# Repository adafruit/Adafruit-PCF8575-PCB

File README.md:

## Adafruit PCF8575 I2C 16 GPIO Expander PCB

<a href="http://www.adafruit.com/products/5611"><br/>
Click here to purchase one from the Adafruit shop</a>

PCB files for the Adafruit PCF8575 I2C 16 GPIO Expander. 

Format is EagleCAD schematic and board layout
* https://www.adafruit.com/product/5611

### Description

Expand your project possibilities, with the Adafruit PCF8575 GPIO Expander Breakout - an affordable 16 channel I2C expander.

GPIO expanders work like this: you have a board with some number of GPIO but not enough for your project - maybe you need more buttons or LEDs. You could upgrade to a board with massive number of GPIO like the Grand Central, or you could pop on one of these boards. Connect it over I2C and then you can send/receive I2C commands to control the GPIO pins to write and read them. It's going to be slower than direct GPIO access, but maybe that doesn't matter if it takes a millisecond instead of a microsecond. You only need the two I2C pins, and you can even share the I2C port with other sensors and devices. Heck, you can even add more expanders for massive I/O control!

The PCF8575 is a common and slightly unusual I2C expander for folks who are used to the MCP230xx series:

* First up, it's very affordable - who doesn't love that?
* It has 16 I/O pins
* Three I2C address select jumpers mean up to 8 expanders to one bus for 64 total GPIO added
* Each pin can be an input with light pull-up or an output sink
* IRQ output will automatically alert you when input pins change value
* This chip does not have a pin direction register. You cannot set the pins as input or output - instead, each pin has two possible states. Basically, you can think of it as an open-drain output with a 100K resistor pull-up built in.
* Option one: Lightly pulled up 'input' - by default it will read as a high logic level, but connecting the GPIO to ground will cause it to read as a low logic level.
* Option two: Strong 20mA low-driving transistor sink output. This means the output is 'forced' to be low and will always read as a low logic level.

The pin direction / state thing is a little odd, but it actually works fine for many purposes as long as you know what to expect.

For example, if you want to read a button or switch, connect one side to the PCF and the other side to ground. Then set the pin to 'light pull-up input' When the button is pressed it will read low, when released it will read high.

If you want to control an LED, connect the anode to positive voltage through a resistor. When the PCF pin is set to 'light pull-up input' the LED will be off. When the PCF pin is set to 'strong ground output' the LED will connect to ground and turn on.

If you want to send a GPIO output logic level to some other device or peripheral, the light pull-up acts as high logic out, the strong ground output acts as low logic out.

If you want to receive a GPIO input logic level, set the pin to light pull-up and then read the pin to determine if the GPIO input is high or low.

Basically, the only thing to watch for is you cannot drive an LED that is expecting the expander GPIO to go high to turn on the LED or connect a button input to a positive voltage without adding an additional pull-down resistor. If this is a bit confusing, worry not - all this stuff is taken care of for you in our Arduino PCF8574/5 library or CircuitPython/Python PCF8575 library - you can pretend it has input/output modes and the library will fake out what you are expecting.

To get you going fast, we spun up a custom-made PCB in the STEMMA QT form factor, making it easy to interface with. The STEMMA QT connectors on either side are compatible with the SparkFun Qwiic I2C connectors. This allows you to make solderless connections between your development board and the PCF8575 or to chain it with a wide range of other sensors and accessories using a compatible cable.

QT Cable is not included, but we have a variety in the shop.

### License

Adafruit invests time and resources providing this open source design, please support Adafruit and open-source hardware by purchasing products from [Adafruit](https://www.adafruit.com)!

Designed by Limor Fried/Ladyada for Adafruit Industries.

Creative Commons Attribution/Share-Alike, all text above must be included in any redistribution. 
See license.txt for additional details.

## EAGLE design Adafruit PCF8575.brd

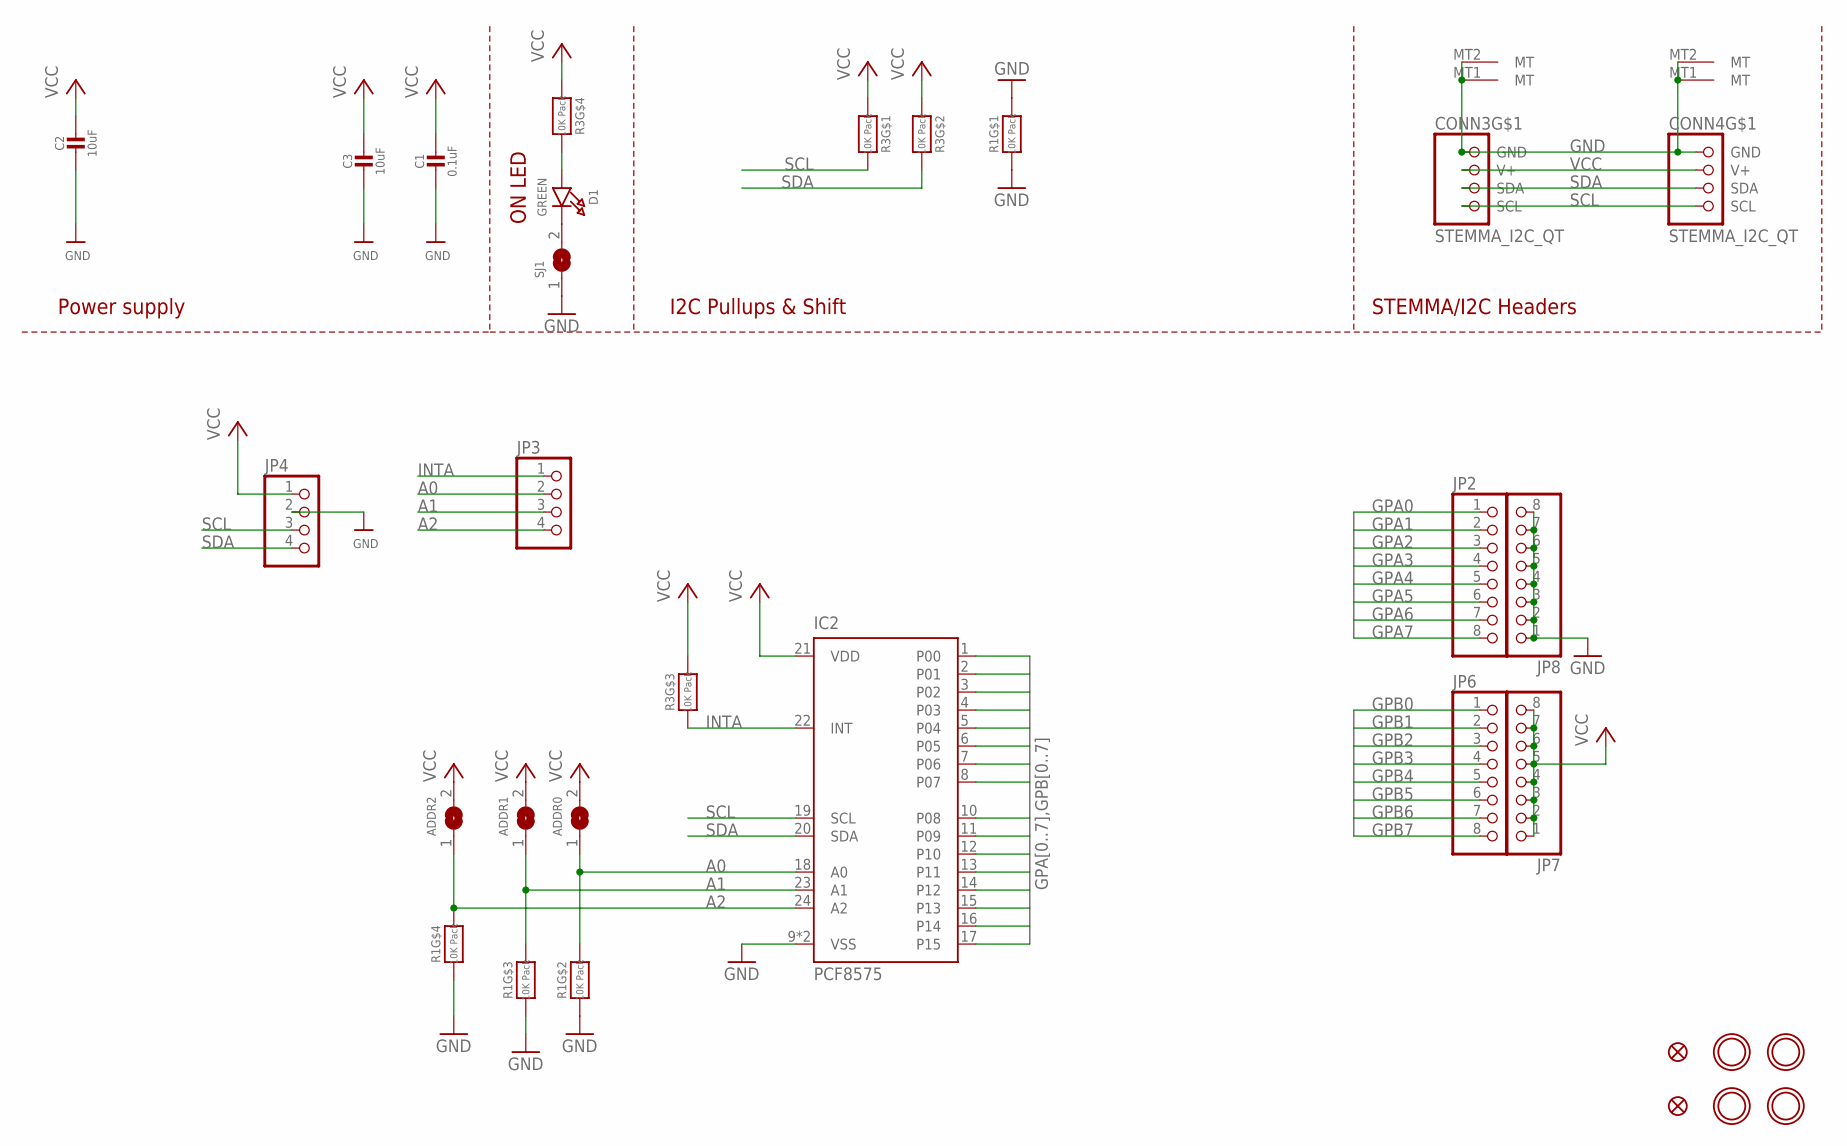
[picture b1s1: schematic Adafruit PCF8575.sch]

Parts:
ADDR0, ADDR1, ADDR2: SOLDERJUMPER; SOLDERJUMPER_ARROW_NOPASTE
C1: 0.1uF; 0603-NO
C2, C3: 10uF; 0805-NO
CONN3, CONN4: STEMMA_I2C_QT; JST_SH4
D1: GREEN; CHIPLED_0603_NOOUTLINE
FID3, FID4: FIDUCIAL_1MM
IC2: PCF8575; QFN24_4MM_SMSC
JP2, JP6, JP7, JP8: HEADER-1X870MIL; 1X08_ROUND_70
JP3, JP4: HEADER-1X4ROUND; 1X04_ROUND
R1, R3: 10K Pack; RESPACK_4X0603
SJ1: SOLDERJUMPERCLOSED; SOLDERJUMPER_CLOSEDWIRE
U$1, U$17, U$19, U$21: MOUNTINGHOLE2.5; MOUNTINGHOLE_2.5_PLATED

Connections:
A0: ADDR0.1, IC2.18 (A0), JP3.2, R1.7 (2)
A1: ADDR1.1, IC2.23 (A1), JP3.3, R1.6 (2)
A2: ADDR2.1, IC2.24 (A2), JP3.4, R1.5 (2)
GND: C1.2, C2.2, C3.2, CONN3.1 (GND), CONN3.MT1 (MT), CONN3.MT2 (MT), CONN4.1 (GND), CONN4.MT1 (MT), CONN4.MT2 (MT), IC2.9 (VSS), IC2.THERM (VSS), JP4.2, JP8.1, JP8.2, JP8.3, JP8.4, JP8.5, JP8.6, JP8.7, JP8.8, R1.1, R1.2 (1), R1.3 (1), R1.4 (1), R1.8 (2), SJ1.1
GPA0: IC2.1 (P00), JP2.1
GPA1: IC2.2 (P01), JP2.2
GPA2: IC2.3 (P02), JP2.3
GPA3: IC2.4 (P03), JP2.4
GPA4: IC2.5 (P04), JP2.5
GPA5: IC2.6 (P05), JP2.6
GPA6: IC2.7 (P06), JP2.7
GPA7: IC2.8 (P07), JP2.8
GPB0: IC2.10 (P08), JP6.1
GPB1: IC2.11 (P09), JP6.2
GPB2: IC2.12 (P10), JP6.3
GPB3: IC2.13 (P11), JP6.4
GPB4: IC2.14 (P12), JP6.5
GPB5: IC2.15 (P13), JP6.6
GPB6: IC2.16 (P14), JP6.7
GPB7: IC2.17 (P15), JP6.8
INTA: IC2.22 (INT), JP3.1, R3.3 (1)
unnamed: D1.A, R3.5 (2)
unnamed: D1.C, SJ1.2
SCL: CONN3.4 (SCL), CONN4.4 (SCL), IC2.19 (SCL), JP4.3, R3.8 (2)
SDA: CONN3.3 (SDA), CONN4.3 (SDA), IC2.20 (SDA), JP4.4, R3.7 (2)
VCC: ADDR0.2, ADDR1.2, ADDR2.2, C1.1, C2.1, C3.1, CONN3.2 (V+), CONN4.2 (V+), IC2.21 (VDD), JP4.1, JP7.1, JP7.2, JP7.3, JP7.4, JP7.5, JP7.6, JP7.7, JP7.8, R3.1, R3.2 (1), R3.4 (1), R3.6 (2)

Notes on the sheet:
I2C Pullups & Shift
STEMMA/I2C Headers
ON LED
Power supply

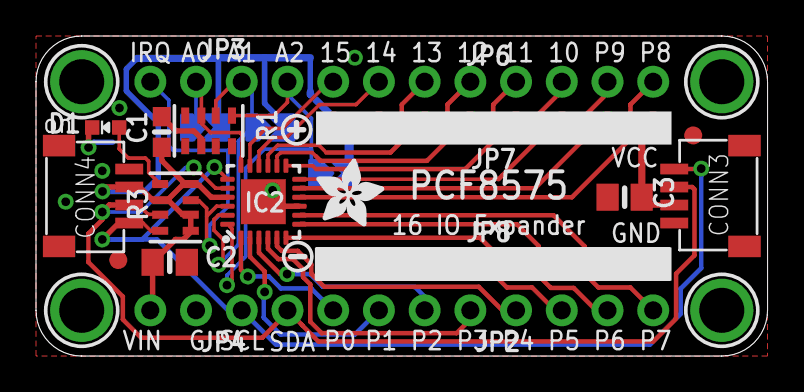
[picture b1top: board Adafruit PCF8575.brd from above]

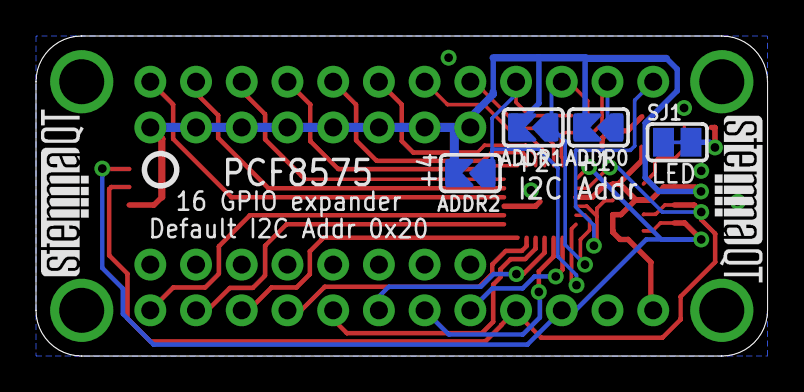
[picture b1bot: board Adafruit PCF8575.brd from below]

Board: 2 copper layers, 40.6 x 17.8 mm, 31 parts (7 on the bottom side), 26 nets.

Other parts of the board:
U$2: SYMBOL_PLUS
U$3: SYMBOL_MINUS
U$22: ADAFRUIT_3.5MM
U$25: PCBFEAT-REV-040
U$30, U$31: STEMMAQT

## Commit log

2022-10-26 Add board files.

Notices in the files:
parts and their libraries:
microbuilder: This work is placed in the public domain, and may be freely used for commercial and non-commercial work with the following conditions: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
